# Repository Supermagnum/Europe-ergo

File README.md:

# Europe-ergo
A 94 key ergonomic,split keyboard.
Its powered by 2X Raspberry pico and linked with two 5 pin D sub connectors.
It uses tht components.

The reset switches, 5 pin D sub connectors and raspberry pico's  goes on the reverse side of the Pcb's. 

Picture of Pcb's top side:
https://github.com/Supermagnum/Europe-ergo/blob/main/Europe-ergo-PCB/Europe-ergo-frontside.jpg

Backside:
https://github.com/Supermagnum/Europe-ergo/blob/main/Europe-ergo-PCB/Europe-ergo-backside.jpg

Layout:
https://github.com/Supermagnum/Europe-ergo/blob/main/layout.png

or:

http://www.keyboard-layout-editor.com/#/gists/50db7ea7b0832342d4c734eb985ec16b

The L1/L2 button is to change from  Norwegian QWERTY to Norwegian Dvorak.
There are relevant LEDs that lights up depending on what layer is active.

The NUM key can be used to turn the  num layer on or off.

Keycaps:
https://github.com/Supermagnum/Europe-ergo/blob/main/keycaps.jpg

prototype/"proof of concept" build pictures:
https://github.com/Supermagnum/Europe-ergo/tree/main/prototype-build

Electronic diagram:
https://github.com/Supermagnum/Europe-ergo/blob/main/Europe-ergo-PCB/schema/Europe-ergo.pdf

All mechanical blueprints as pdf files can be exported from the Freecad file.
Freecad can be found for free here:
https://www.freecadweb.org/

PWM1 to PWM 5 controls LED's ( ON/OFF) based by the active layer, and also caps lock and scroll lock active.

Those and the electrical diagram can be found here:
https://github.com/Supermagnum/Europe-ergo/blob/main/Europe-ergo-PCB/schema/Europe-ergo.pdf
The right side has identical outputs for PWM.

Cherry MX switches fit the PCB'S.

Missing from the BOM:
Keyswitch Hotswap sockets: 0305-2-15-80-47-80-10-0 or Digikey: ED90584-ND

STL files for 3D printing or milling of the boxes:
https://github.com/Supermagnum/Europe-ergo/tree/main/mechanical

Tool for aligning the switches under soldering, slips on to the PCB edge an over the switch:
https://github.com/Supermagnum/Europe-ergo/blob/main/mechanical/STL/switch-tool.stl

Panelized version:
https://github.com/Supermagnum/erope-ergo-ex

License:
https://github.com/Supermagnum/Europe-ergo/blob/main/LICENSE

 "

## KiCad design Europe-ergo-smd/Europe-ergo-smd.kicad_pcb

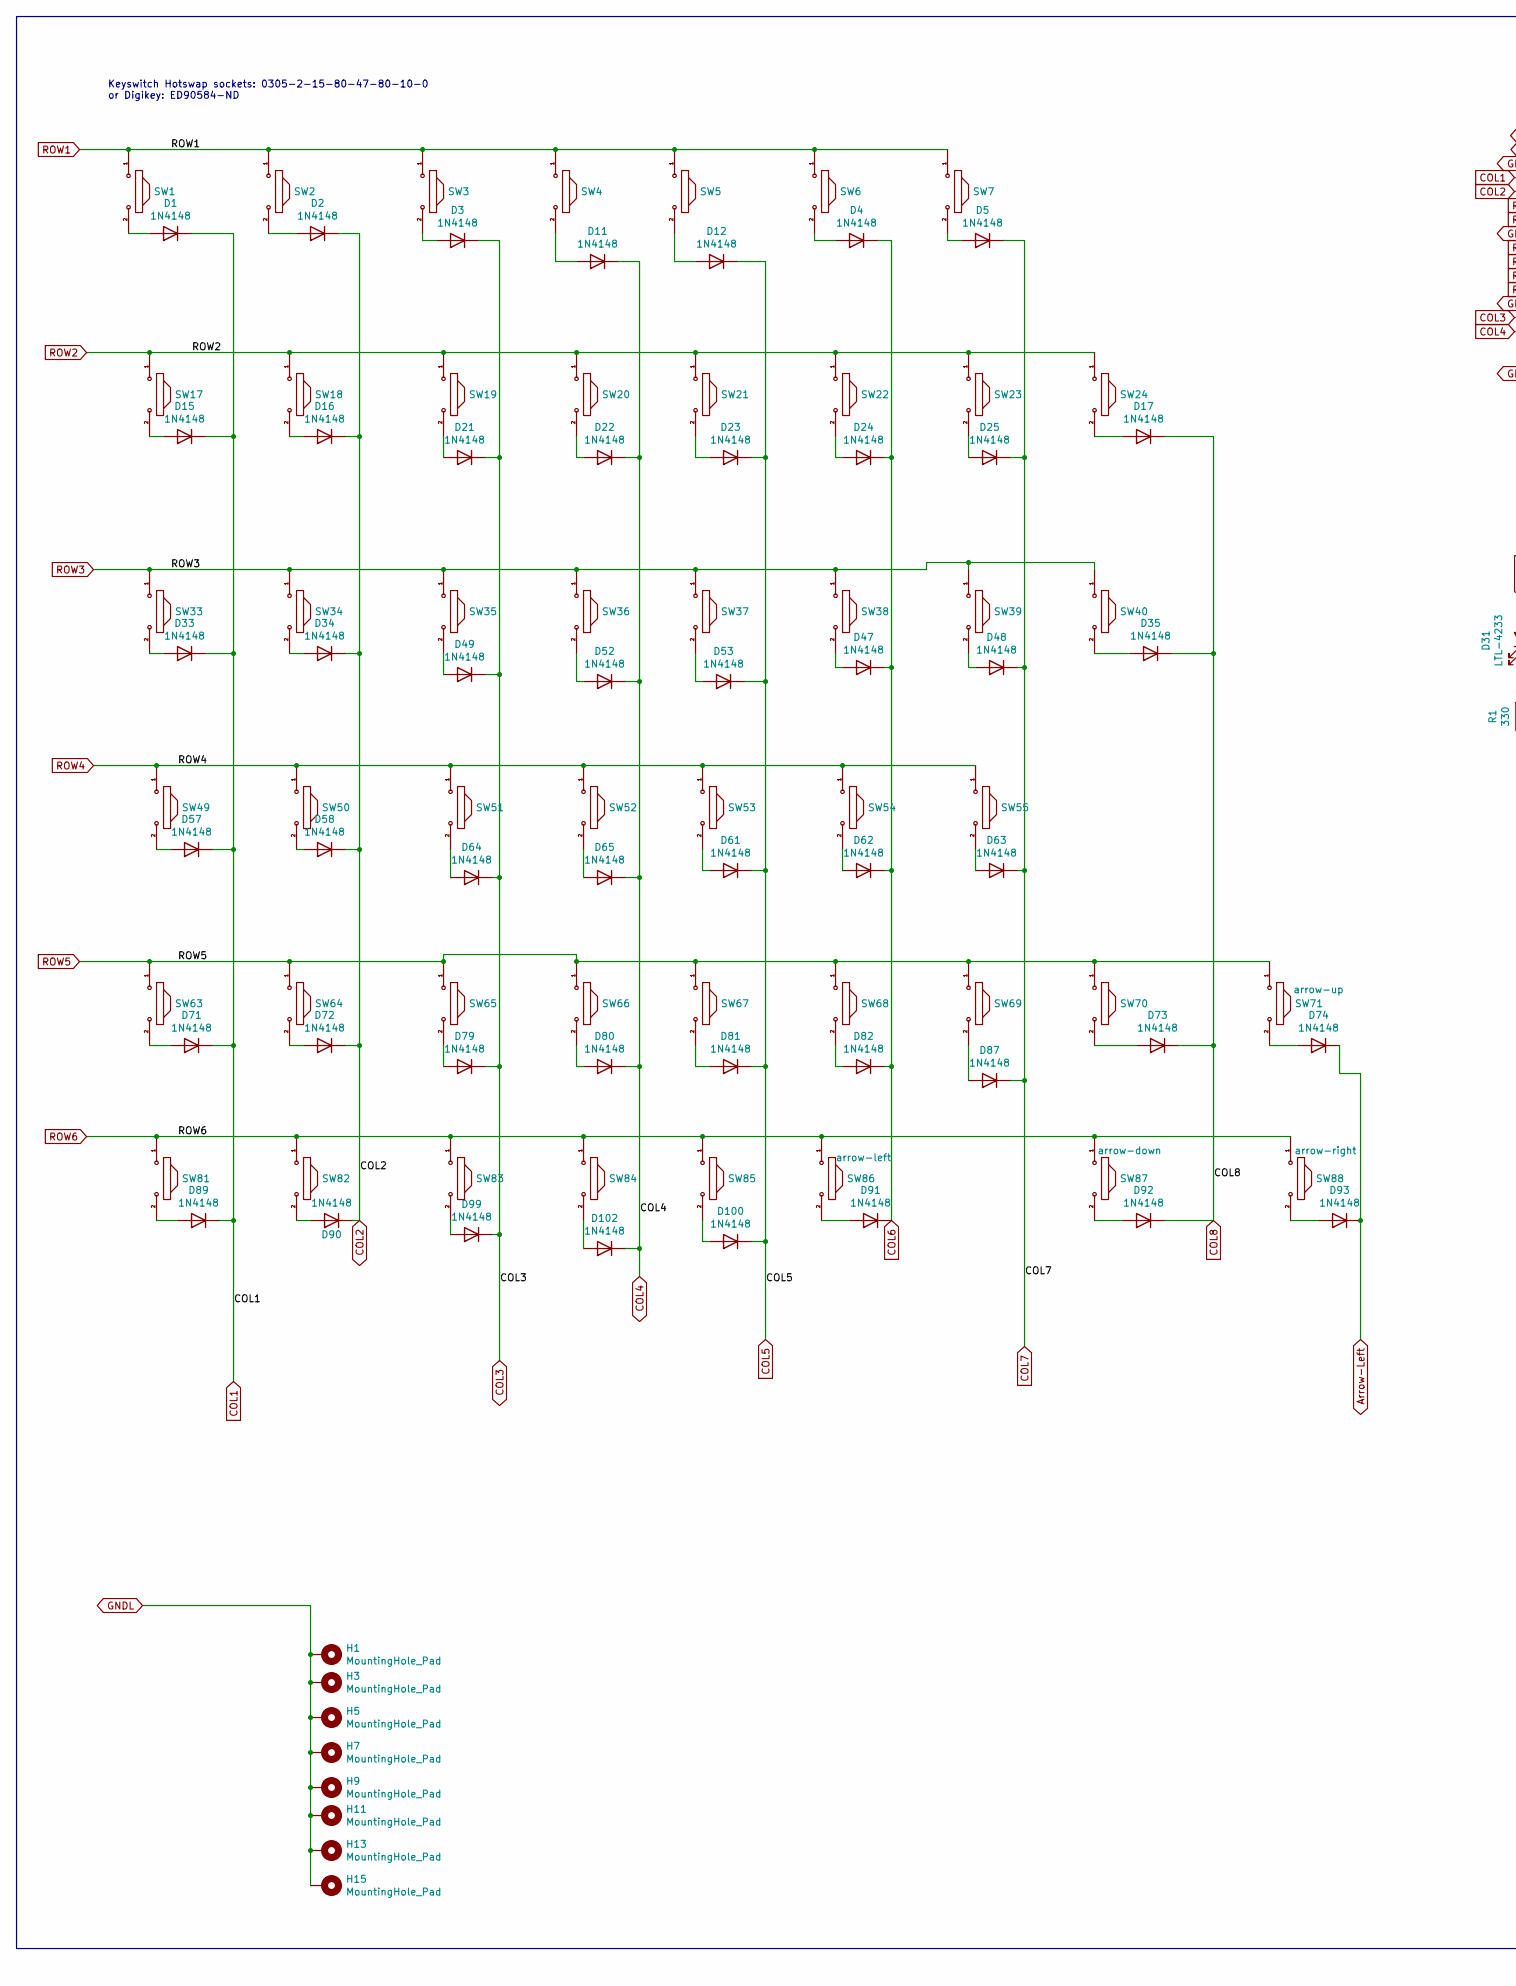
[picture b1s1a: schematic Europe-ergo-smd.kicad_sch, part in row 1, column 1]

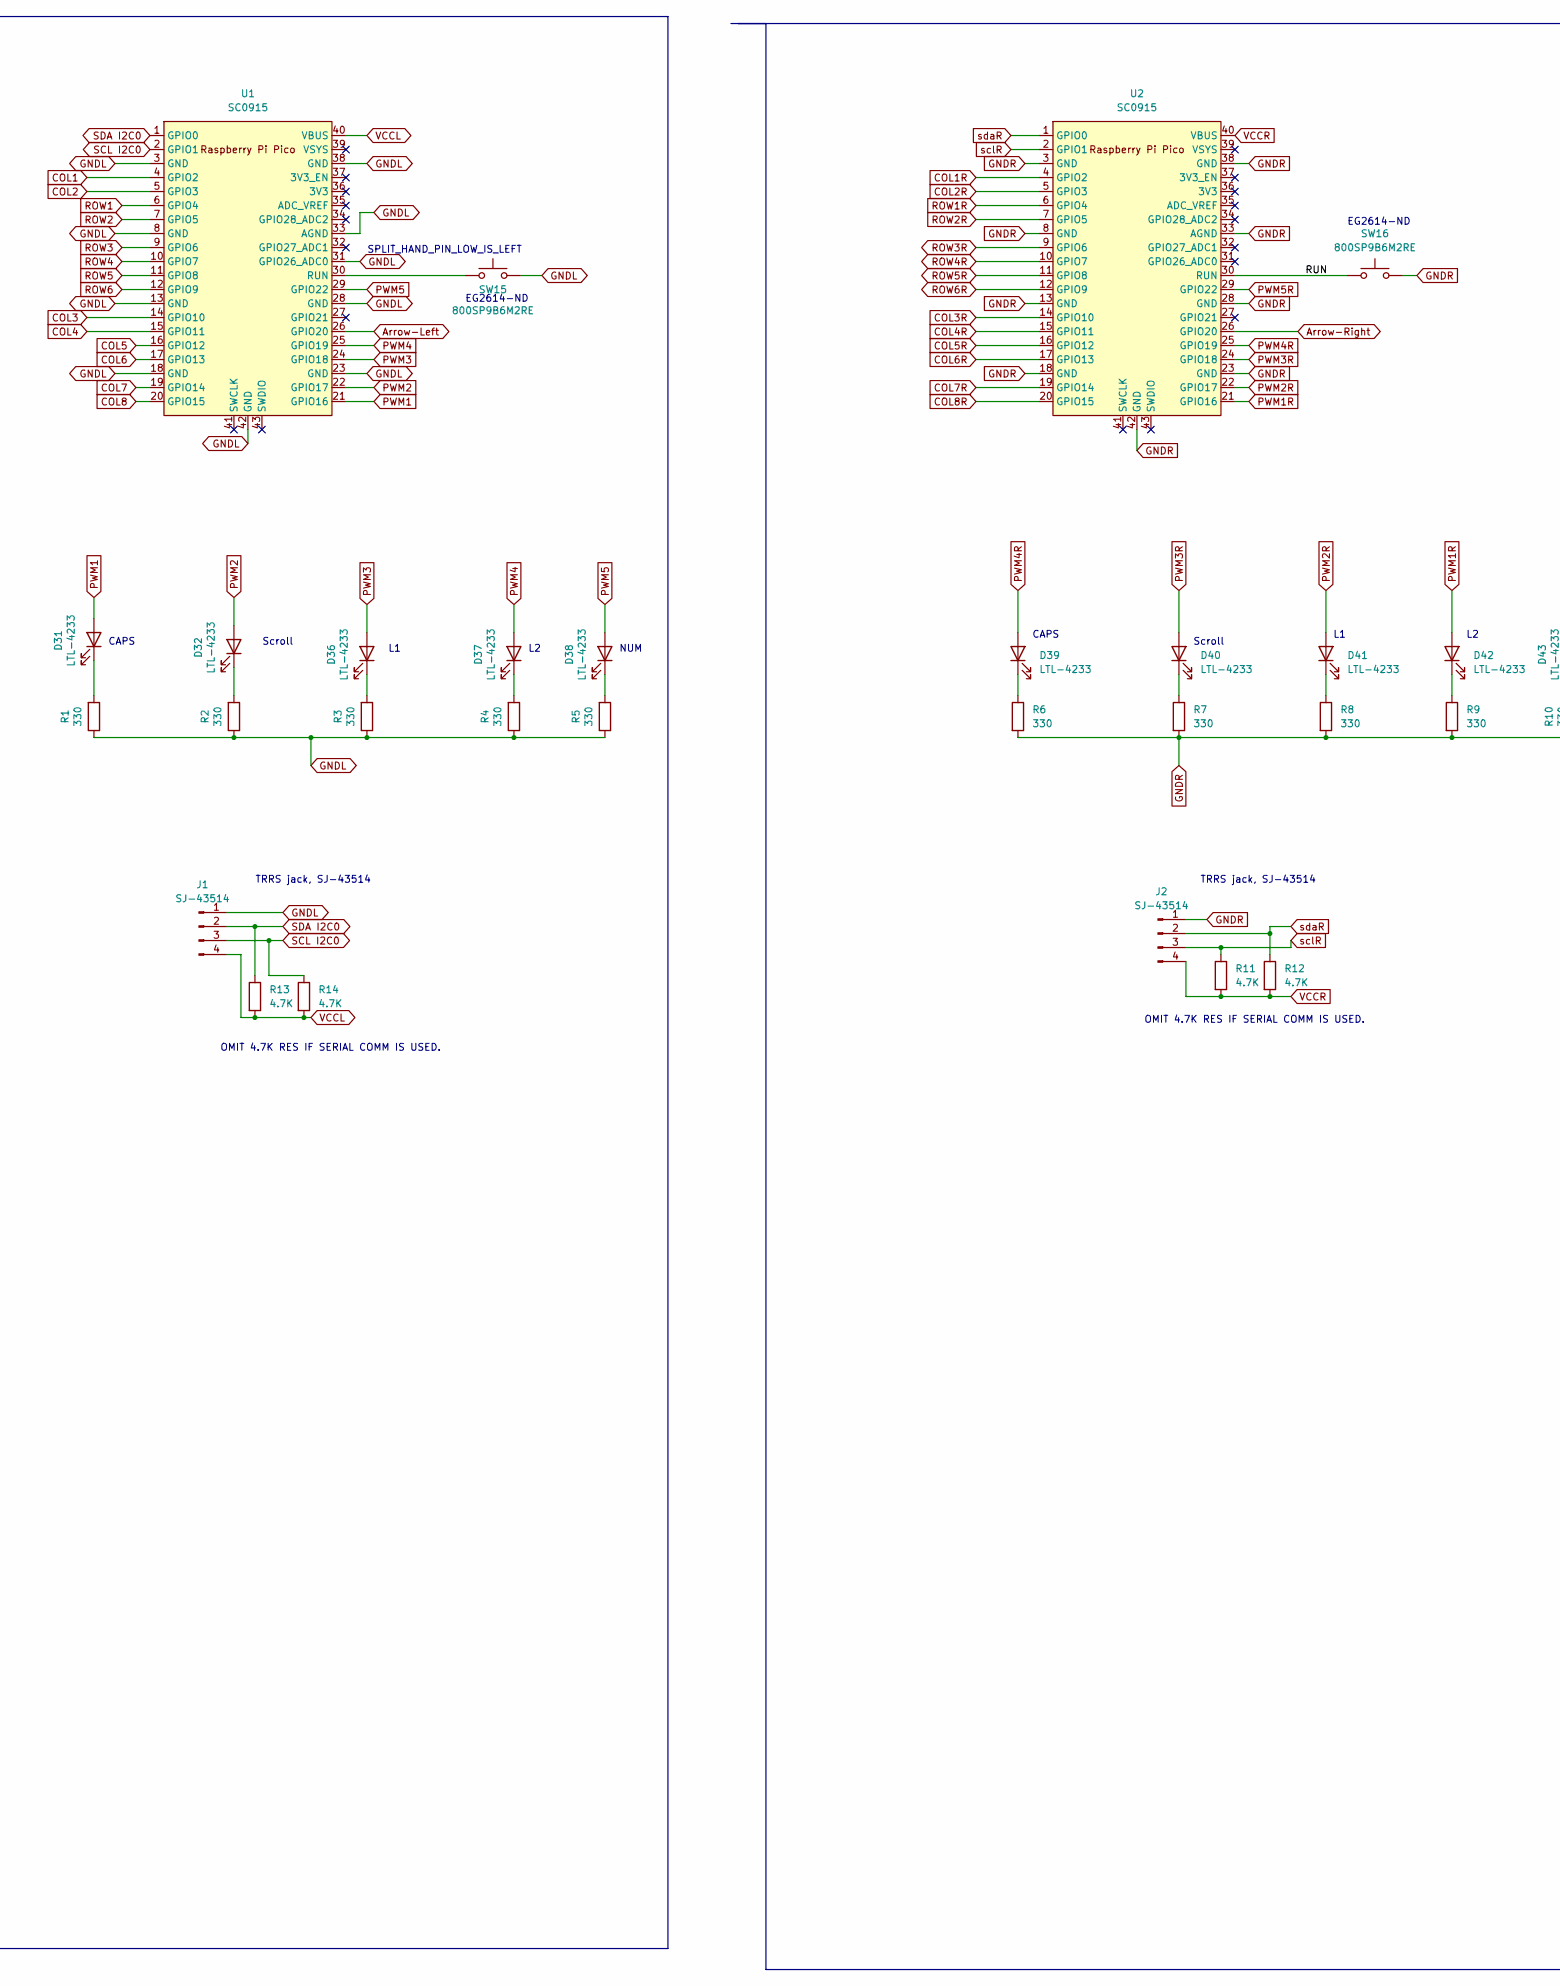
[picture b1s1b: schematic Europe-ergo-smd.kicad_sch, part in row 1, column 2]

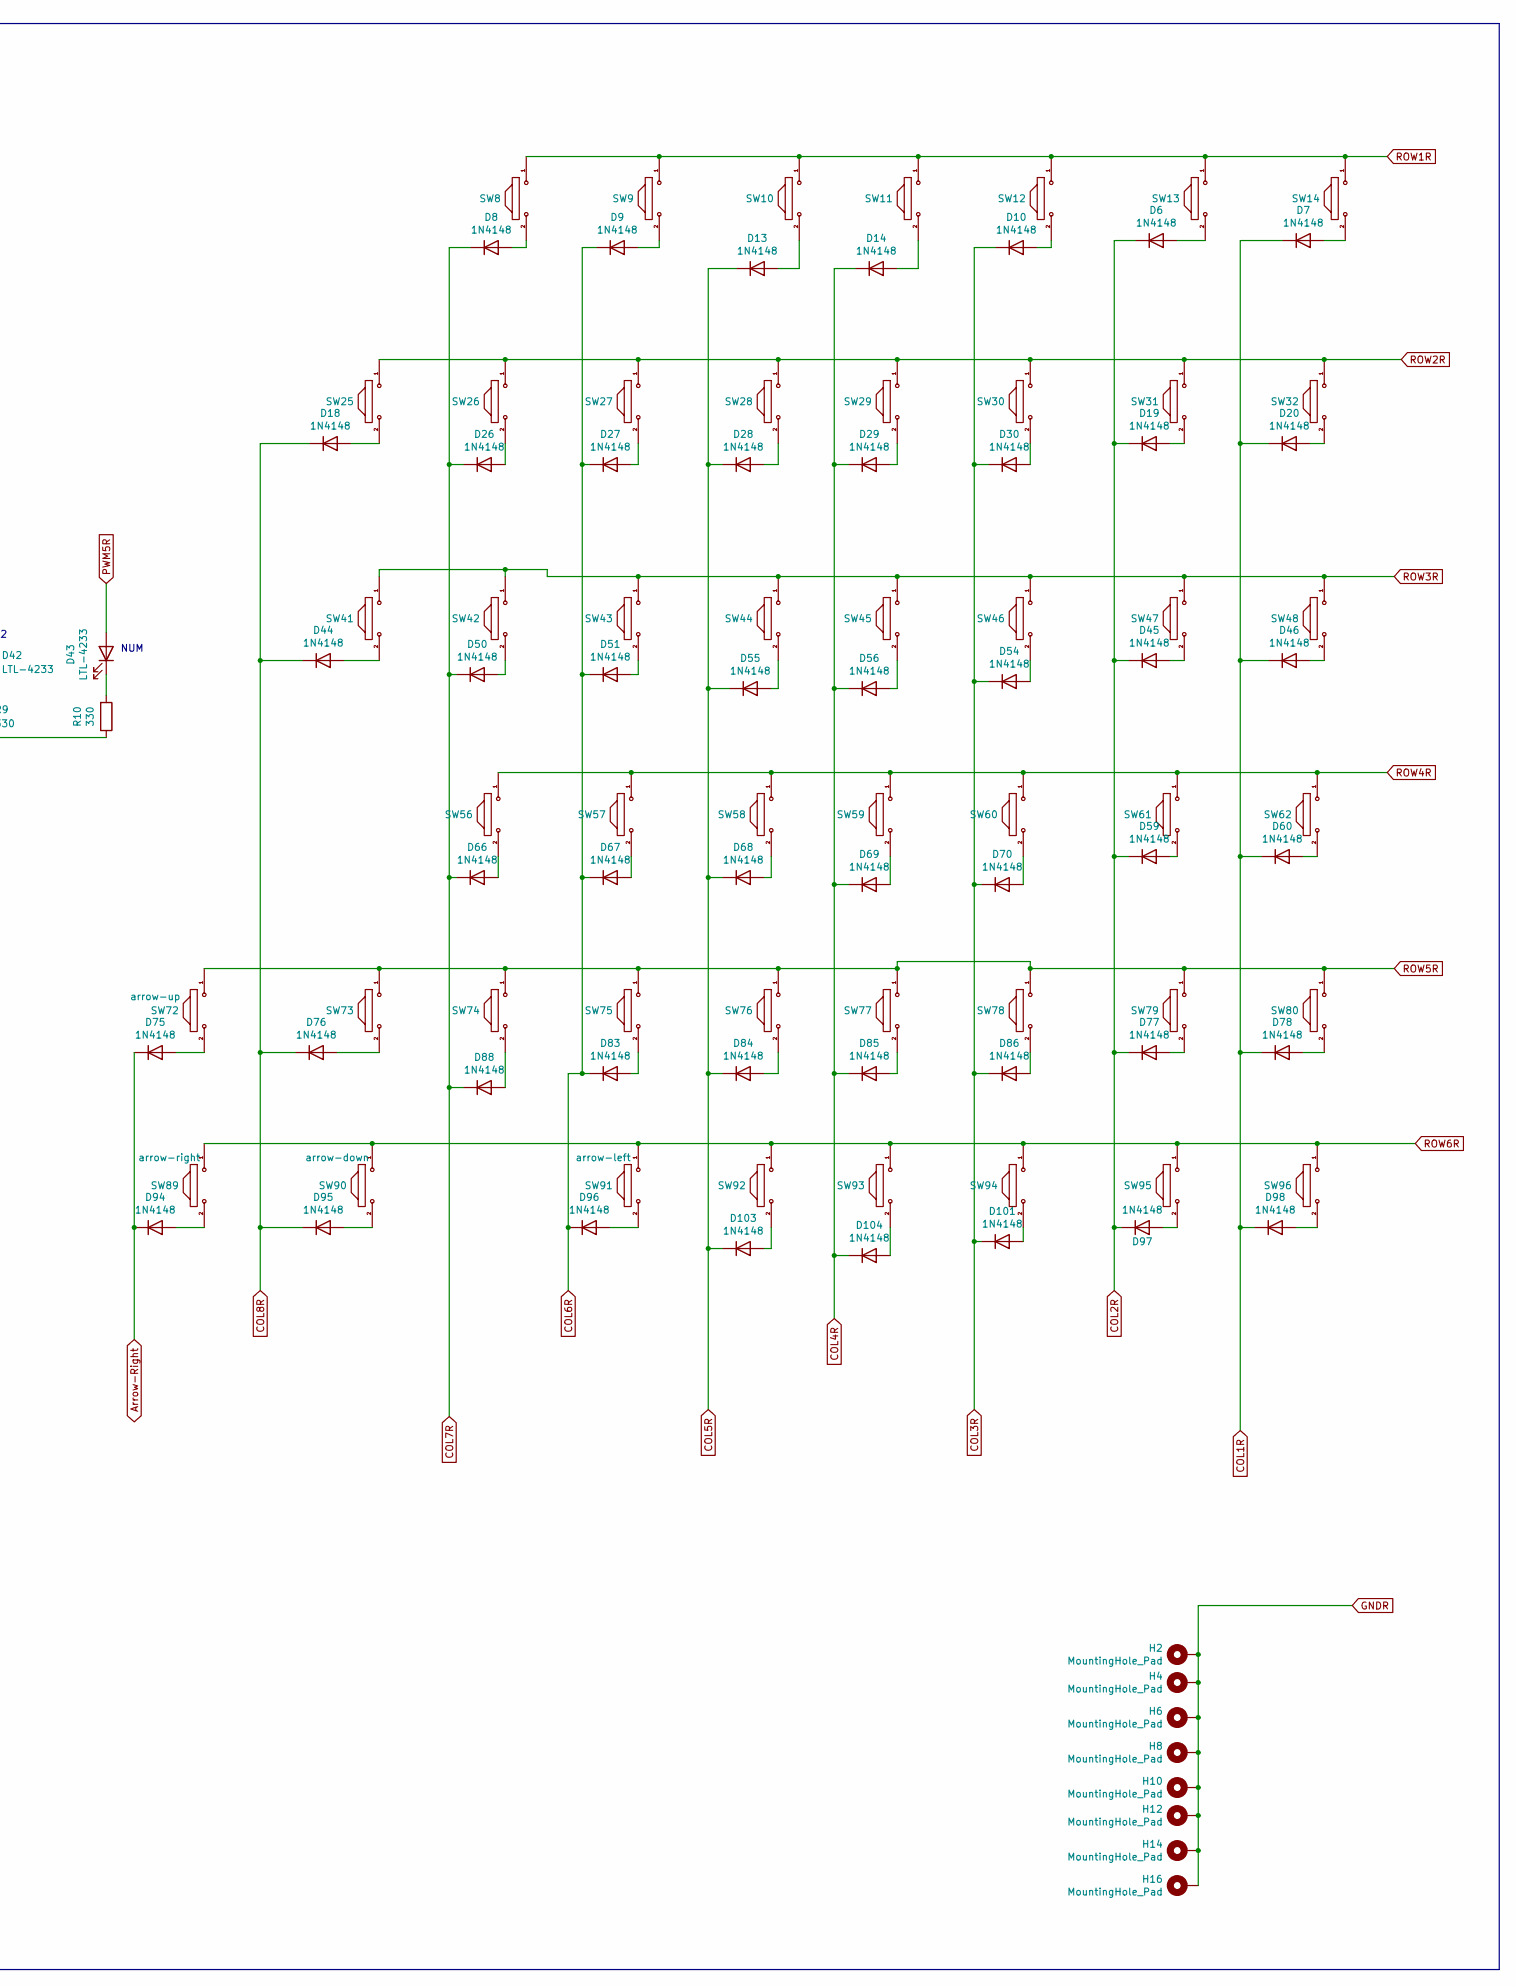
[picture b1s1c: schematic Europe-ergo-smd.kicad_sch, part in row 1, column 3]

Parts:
D1, D2, D3, D4, D5, D6, D7, D8, D9, D10, D11, D12, D13, D14, D15, D16, D17, D18, D19, D20, D21, D22, D23, D24, D25, D26, D27, D28, D29, D30, D33, D34, D35, D44, D45, D46, D47, D48, D49, D50, D51, D52, D53, D54, D55, D56, D57, D58, D59, D60, D61, D62, D63, D64, D65, D66, D67, D68, D69, D70, D71, D72, D73, D74, D75, D76, D77, D78, D79, D80, D81, D82, D83, D84, D85, D86, D87, D88, D89, D90, D91, D92, D93, D94, D95, D96, D97, D98, D99, D100, D101, D102, D103, D104: 1N4148; D_1812_4532Metric
D31, D32, D36, D37, D38, D43: LTL-4233; D_A-405_P2.54mm_Vertical_AnodeUp
D39, D40, D41, D42: LTL-4233; D_DO-34_SOD68_P2.54mm_Vertical_KathodeUp
H1, H2, H3, H4, H5, H6, H7, H8, H9, H10, H11, H12, H13, H14, H15, H16: MountingHole_Pad; MountingHole_4.3mm_M4_DIN965_Pad
J1, J2: SJ-43514; CUI_SJ-43514
R1, R2, R3, R4, R5, R6, R7, R8, R9, R10: 330; R_1812_4532Metric
R11, R12, R13, R14: 4.7K; R_1812_4532Metric
SW1, SW2, SW3, SW4, SW5, SW6, SW7, SW8, SW9, SW10, SW11, SW12, SW13, SW14, SW18, SW19, SW20, SW21, SW22, SW23, SW24, SW25, SW26, SW27, SW28, SW29, SW30, SW31, SW34, SW35, SW36, SW37, SW38, SW39, SW42, SW43, SW44, SW45, SW46, SW47, SW50, SW51, SW52, SW53, SW54, SW55, SW56, SW57, SW58, SW59, SW60, SW61, SW64, SW65, SW66, SW67, SW68, SW69, SW71, SW72, SW74, SW75, SW76, SW77, SW78, SW79, SW81, SW82, SW83, SW84, SW85, SW86, SW87, SW88, SW89, SW90, SW91, SW92, SW93, SW94, SW95, SW96: MX1A-G1NN; SW_Cherry_MX_1.00u_PCB
SW15, SW16: 800SP9B6M2RE; switch_P5.08mm
SW17, SW32, SW33, SW40, SW41, SW48, SW49, SW62, SW63, SW70, SW73, SW80: MX1A-G1NN; SW_Cherry_MX_1.50u_PCB
U1, U2: SC0915; RPi_Pico_SMD_TH

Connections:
/RUN: SW16.1, U2.30 (RUN)
Arrow-Left: D74.1 (K), D93.1 (K), U1.26 (GPIO20)
Arrow-Right: D75.1 (K), D94.1 (K), U2.26 (GPIO20)
COL1: D1.1 (K), D15.1 (K), D33.1 (K), D57.1 (K), D71.1 (K), D89.1 (K), U1.4 (GPIO2)
COL1R: D7.1 (K), D20.1 (K), D46.1 (K), D60.1 (K), D78.1 (K), D98.1 (K), U2.4 (GPIO2)
COL2: D2.1 (K), D16.1 (K), D34.1 (K), D58.1 (K), D72.1 (K), D90.1 (K), U1.5 (GPIO3)
COL2R: D6.1 (K), D19.1 (K), D45.1 (K), D59.1 (K), D77.1 (K), D97.1 (K), U2.5 (GPIO3)
COL3: D3.1 (K), D21.1 (K), D49.1 (K), D64.1 (K), D79.1 (K), D99.1 (K), U1.14 (GPIO10)
COL3R: D10.1 (K), D30.1 (K), D54.1 (K), D70.1 (K), D86.1 (K), D101.1 (K), U2.14 (GPIO10)
COL4: D11.1 (K), D22.1 (K), D52.1 (K), D65.1 (K), D80.1 (K), D102.1 (K), U1.15 (GPIO11)
COL4R: D14.1 (K), D29.1 (K), D56.1 (K), D69.1 (K), D85.1 (K), D104.1 (K), U2.15 (GPIO11)
COL5: D12.1 (K), D23.1 (K), D53.1 (K), D61.1 (K), D81.1 (K), D100.1 (K), U1.16 (GPIO12)
COL5R: D13.1 (K), D28.1 (K), D55.1 (K), D68.1 (K), D84.1 (K), D103.1 (K), U2.16 (GPIO12)
COL6: D4.1 (K), D24.1 (K), D47.1 (K), D62.1 (K), D82.1 (K), D91.1 (K), U1.17 (GPIO13)
COL6R: D9.1 (K), D27.1 (K), D51.1 (K), D67.1 (K), D83.1 (K), D96.1 (K), U2.17 (GPIO13)
COL7: D5.1 (K), D25.1 (K), D48.1 (K), D63.1 (K), D87.1 (K), U1.19 (GPIO14)
COL7R: D8.1 (K), D26.1 (K), D50.1 (K), D66.1 (K), D88.1 (K), U2.19 (GPIO14)
COL8: D17.1 (K), D35.1 (K), D73.1 (K), D92.1 (K), U1.20 (GPIO15)
COL8R: D18.1 (K), D44.1 (K), D76.1 (K), D95.1 (K), U2.20 (GPIO15)
GNDL: H1.1, H3.1, H5.1, H7.1, H9.1, H11.1, H13.1, H15.1, J1.1, R1.1, R2.1, R3.1, R4.1, R5.1, SW15.2, U1.3 (GND), U1.8 (GND), U1.13 (GND), U1.18 (GND), U1.23 (GND), U1.28 (GND), U1.31 (GPIO26_ADC0), U1.33 (AGND), U1.38 (GND), U1.42 (GND)
GNDR: H2.1, H4.1, H6.1, H8.1, H10.1, H12.1, H14.1, H16.1, J2.1, R6.2, R7.2, R8.2, R9.2, R10.1, SW16.2, U2.3 (GND), U2.8 (GND), U2.13 (GND), U2.18 (GND), U2.23 (GND), U2.28 (GND), U2.33 (AGND), U2.38 (GND), U2.42 (GND)
unnamed: D1.2 (A), SW1.2
unnamed: D2.2 (A), SW2.2
unnamed: D3.2 (A), SW3.2
unnamed: D4.2 (A), SW6.2
unnamed: D5.2 (A), SW7.2
unnamed: D6.2 (A), SW13.2
unnamed: D7.2 (A), SW14.2
unnamed: D8.2 (A), SW8.2
unnamed: D9.2 (A), SW9.2
unnamed: D10.2 (A), SW12.2
unnamed: D11.2 (A), SW4.2
unnamed: D12.2 (A), SW5.2
unnamed: D13.2 (A), SW10.2
unnamed: D14.2 (A), SW11.2
unnamed: D15.2 (A), SW17.2
unnamed: D16.2 (A), SW18.2
unnamed: D17.2 (A), SW24.2
unnamed: D18.2 (A), SW25.2
unnamed: D19.2 (A), SW31.2
unnamed: D20.2 (A), SW32.2
unnamed: D21.2 (A), SW19.2
unnamed: D22.2 (A), SW20.2
unnamed: D23.2 (A), SW21.2
unnamed: D24.2 (A), SW22.2
unnamed: D25.2 (A), SW23.2
unnamed: D26.2 (A), SW26.2
unnamed: D27.2 (A), SW27.2
unnamed: D28.2 (A), SW28.2
unnamed: D29.2 (A), SW29.2
unnamed: D30.2 (A), SW30.2
unnamed: D31.1 (K), R1.2
unnamed: D32.1 (K), R2.2
unnamed: D33.2 (A), SW33.2
unnamed: D34.2 (A), SW34.2
unnamed: D35.2 (A), SW40.2
unnamed: D36.1 (K), R3.2
unnamed: D37.1 (K), R4.2
unnamed: D38.1 (K), R5.2
unnamed: D39.1 (K), R6.1
unnamed: D40.1 (K), R7.1
unnamed: D41.1 (K), R8.1
unnamed: D42.1 (K), R9.1
unnamed: D43.1 (K), R10.2
unnamed: D44.2 (A), SW41.2
unnamed: D45.2 (A), SW47.2
unnamed: D46.2 (A), SW48.2
unnamed: D47.2 (A), SW38.2
unnamed: D48.2 (A), SW39.2
unnamed: D49.2 (A), SW35.2
unnamed: D50.2 (A), SW42.2
unnamed: D51.2 (A), SW43.2
unnamed: D52.2 (A), SW36.2
unnamed: D53.2 (A), SW37.2
unnamed: D54.2 (A), SW46.2
unnamed: D55.2 (A), SW44.2
unnamed: D56.2 (A), SW45.2
unnamed: D57.2 (A), SW49.2
unnamed: D58.2 (A), SW50.2
unnamed: D59.2 (A), SW61.2
unnamed: D60.2 (A), SW62.2
unnamed: D61.2 (A), SW53.2
unnamed: D62.2 (A), SW54.2
unnamed: D63.2 (A), SW55.2
unnamed: D64.2 (A), SW51.2
unnamed: D65.2 (A), SW52.2
unnamed: D66.2 (A), SW56.2
unnamed: D67.2 (A), SW57.2
unnamed: D68.2 (A), SW58.2
unnamed: D69.2 (A), SW59.2
unnamed: D70.2 (A), SW60.2
unnamed: D71.2 (A), SW63.2
unnamed: D72.2 (A), SW64.2
unnamed: D73.2 (A), SW70.2
unnamed: D74.2 (A), SW71.2
unnamed: D75.2 (A), SW72.2
unnamed: D76.2 (A), SW73.2
unnamed: D77.2 (A), SW79.2
unnamed: D78.2 (A), SW80.2
unnamed: D79.2 (A), SW65.2
unnamed: D80.2 (A), SW66.2
unnamed: D81.2 (A), SW67.2
unnamed: D82.2 (A), SW68.2
unnamed: D83.2 (A), SW75.2
unnamed: D84.2 (A), SW76.2
unnamed: D85.2 (A), SW77.2
unnamed: D86.2 (A), SW78.2
unnamed: D87.2 (A), SW69.2
unnamed: D88.2 (A), SW74.2
unnamed: D89.2 (A), SW81.2
unnamed: D90.2 (A), SW82.2
unnamed: D91.2 (A), SW86.2
unnamed: D92.2 (A), SW87.2
unnamed: D93.2 (A), SW88.2
unnamed: D94.2 (A), SW89.2
unnamed: D95.2 (A), SW90.2
unnamed: D96.2 (A), SW91.2
unnamed: D97.2 (A), SW95.2
unnamed: D98.2 (A), SW96.2
unnamed: D99.2 (A), SW83.2
unnamed: D100.2 (A), SW85.2
unnamed: D101.2 (A), SW94.2
unnamed: D102.2 (A), SW84.2
unnamed: D103.2 (A), SW92.2
unnamed: D104.2 (A), SW93.2
unnamed: SW15.1, U1.30 (RUN)
PWM1: D31.2 (A), U1.21 (GPIO16)
PWM1R: D42.2 (A), U2.21 (GPIO16)
PWM2: D32.2 (A), U1.22 (GPIO17)
PWM2R: D41.2 (A), U2.22 (GPIO17)
PWM3: D36.2 (A), U1.24 (GPIO18)
PWM3R: D40.2 (A), U2.24 (GPIO18)
PWM4: D37.2 (A), U1.25 (GPIO19)
PWM4R: D39.2 (A), U2.25 (GPIO19)
PWM5: D38.2 (A), U1.29 (GPIO22)
PWM5R: D43.2 (A), U2.29 (GPIO22)
ROW1: SW1.1, SW2.1, SW3.1, SW4.1, SW5.1, SW6.1, SW7.1, U1.6 (GPIO4)
ROW1R: SW8.1, SW9.1, SW10.1, SW11.1, SW12.1, SW13.1, SW14.1, U2.6 (GPIO4)
ROW2: SW17.1, SW18.1, SW19.1, SW20.1, SW21.1, SW22.1, SW23.1, SW24.1, U1.7 (GPIO5)
ROW2R: SW25.1, SW26.1, SW27.1, SW28.1, SW29.1, SW30.1, SW31.1, SW32.1, U2.7 (GPIO5)
ROW3: SW33.1, SW34.1, SW35.1, SW36.1, SW37.1, SW38.1, SW39.1, SW40.1, U1.9 (GPIO6)
ROW3R: SW41.1, SW42.1, SW43.1, SW44.1, SW45.1, SW46.1, SW47.1, SW48.1, U2.9 (GPIO6)
ROW4: SW49.1, SW50.1, SW51.1, SW52.1, SW53.1, SW54.1, SW55.1, U1.10 (GPIO7)
ROW4R: SW56.1, SW57.1, SW58.1, SW59.1, SW60.1, SW61.1, SW62.1, U2.10 (GPIO7)
ROW5: SW63.1, SW64.1, SW65.1, SW66.1, SW67.1, SW68.1, SW69.1, SW70.1, SW71.1, U1.11 (GPIO8)
ROW5R: SW72.1, SW73.1, SW74.1, SW75.1, SW76.1, SW77.1, SW78.1, SW79.1, SW80.1, U2.11 (GPIO8)
ROW6: SW81.1, SW82.1, SW83.1, SW84.1, SW85.1, SW86.1, SW87.1, SW88.1, U1.12 (GPIO9)
ROW6R: SW89.1, SW90.1, SW91.1, SW92.1, SW93.1, SW94.1, SW95.1, SW96.1, U2.12 (GPIO9)
SCL I2C0: J1.3, R14.1, U1.2 (GPIO1)
SDA I2C0: J1.2, R13.1, U1.1 (GPIO0)
VCCL: J1.4, R13.2, R14.2, U1.40 (VBUS)
VCCR: J2.4, R11.2, R12.2, U2.40 (VBUS)
sclR: J2.3, R11.1, U2.2 (GPIO1)
sdaR: J2.2, R12.1, U2.1 (GPIO0)

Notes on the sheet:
EG2614-ND
Keyswitch Hotswap sockets: 0305-2-15-80-47-80-10-0 or Digikey: ED90584-ND
CAPS
Scroll
OMIT 4.7K RES IF SERIAL COMM IS USED.
SPLIT_HAND_PIN_LOW_IS_LEFT
NUM
TRRS jack, SJ-43514

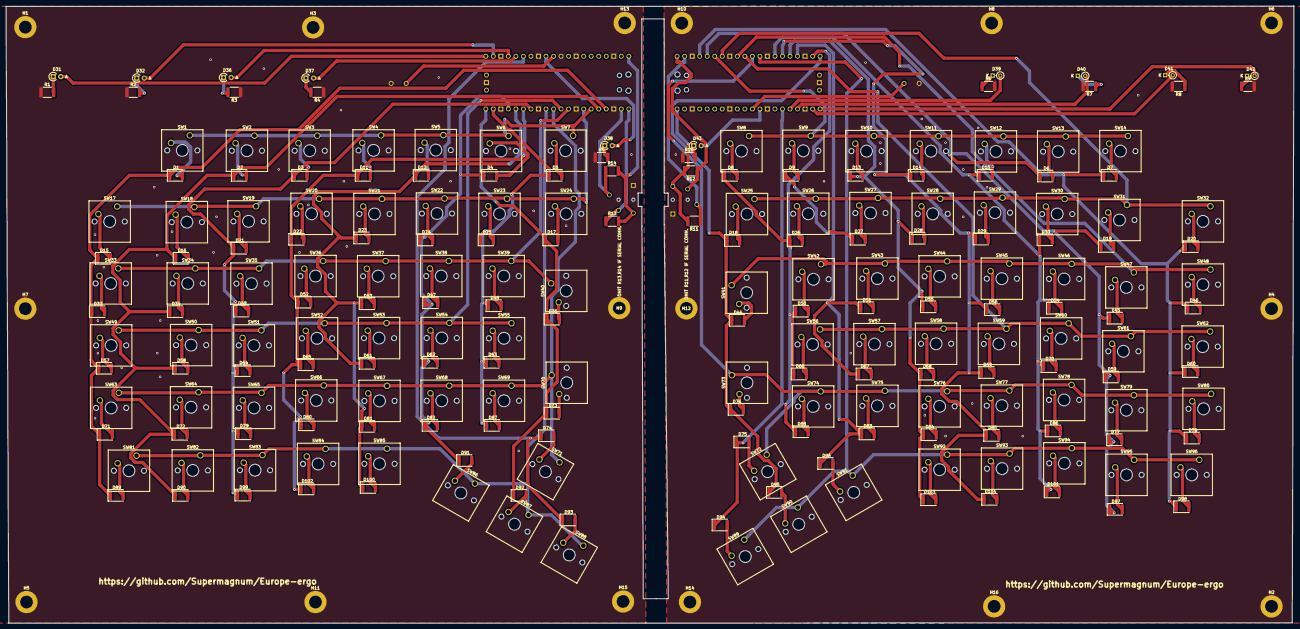
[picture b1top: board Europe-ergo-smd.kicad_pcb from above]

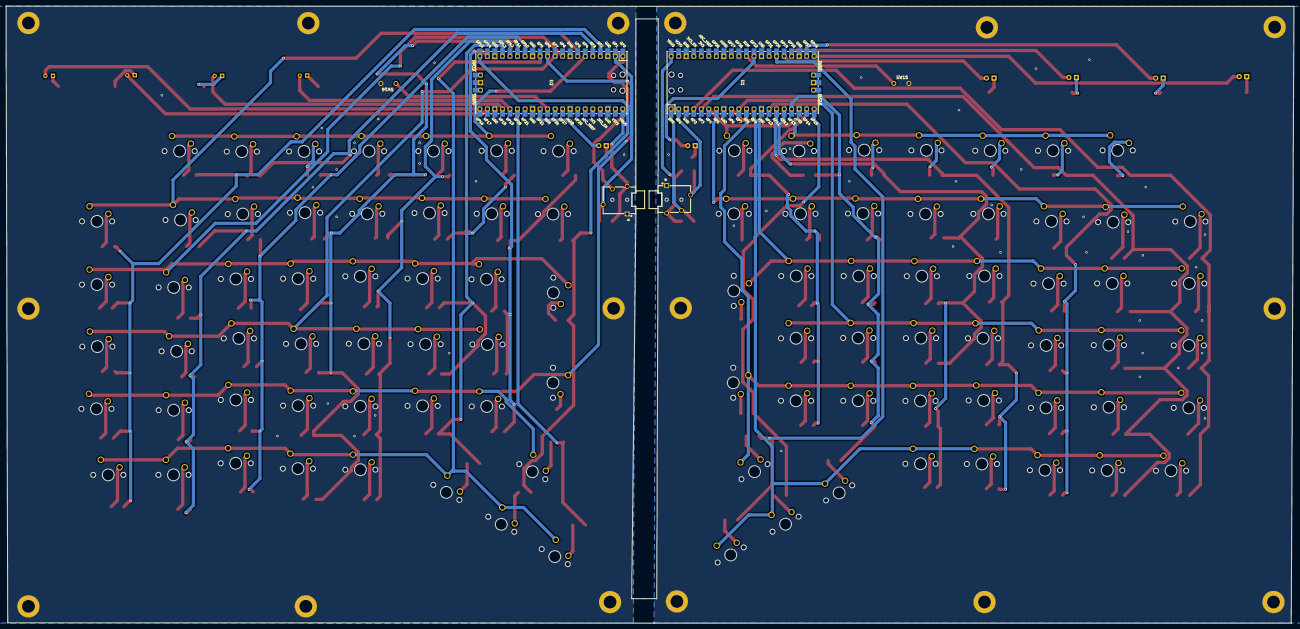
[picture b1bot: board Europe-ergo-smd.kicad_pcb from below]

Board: 2 copper layers, 434.5 x 208.2 mm, 234 parts (6 on the bottom side), 154 nets.

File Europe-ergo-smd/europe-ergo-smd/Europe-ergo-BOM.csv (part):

Source:,/mnt/b955457f-512b-4f44-a0f7-8e5f2b78aba2/Europe-ergo/Europe-ergo-PCB/Europe-ergo.kicad_sch,,,,,,
Date:,fr. 20. jan. 2023 kl. 16.28 +0100,,,,,,
Tool:,Eeschema 6.0.10-86aedd382b~118~ubuntu22.04.1,,,,,,
Generator:,/usr/share/kicad/plugins/bom_csv_grouped_by_value.py,,,,,,
Component Count:,230,,,,,,
,,,,,,,
Individual Components:,,,,,,,
,,,,,,,
Item,Qty,Reference(s),Value,LibPart,Footprint,Datasheet,Field4
,,D1,1N4148,Diode:1N4148,Diode_THT:D_DO-35_SOD27_P7.62mm_Horizontal,https://assets.nexperia.com/documents/data-sheet/1N4148_1N4448.pdf,
,,D2,1N4148,Diode:1N4148,Diode_THT:D_DO-35_SOD27_P7.62mm_Horizontal,https://assets.nexperia.com/documents/data-sheet/1N4148_1N4448.pdf,
,,D3,1N4148,Diode:1N4148,Diode_THT:D_DO-35_SOD27_P7.62mm_Horizontal,https://assets.nexperia.com/documents/data-sheet/1N4148_1N4448.pdf,
,,D4,1N4148,Diode:1N4148,Diode_THT:D_DO-35_SOD27_P7.62mm_Horizontal,https://assets.nexperia.com/documents/data-sheet/1N4148_1N4448.pdf,
,,D5,1N4148,Diode:1N4148,Diode_THT:D_DO-35_SOD27_P7.62mm_Horizontal,https://assets.nexperia.com/documents/data-sheet/1N4148_1N4448.pdf,
,,D6,1N4148,Diode:1N4148,Diode_THT:D_DO-35_SOD27_P7.62mm_Horizontal,https://assets.nexperia.com/documents/data-sheet/1N4148_1N4448.pdf,
,,D7,1N4148,Diode:1N4148,Diode_THT:D_DO-35_SOD27_P7.62mm_Horizontal,https://assets.nexperia.com/documents/data-sheet/1N4148_1N4448.pdf,
,,D8,1N4148,Diode:1N4148,Diode_THT:D_DO-35_SOD27_P7.62mm_Horizontal,https://assets.nexperia.com/documents/data-sheet/1N4148_1N4448.pdf,
,,D9,1N4148,Diode:1N4148,Diode_THT:D_DO-35_SOD27_P7.62mm_Horizontal,https://assets.nexperia.com/documents/data-sheet/1N4148_1N4448.pdf,
,,D10,1N4148,Diode:1N4148,Diode_THT:D_DO-35_SOD27_P7.62mm_Horizontal,https://assets.nexperia.com/documents/data-sheet/1N4148_1N4448.pdf,
,,D11,1N4148,Diode:1N4148,Diode_THT:D_DO-35_SOD27_P7.62mm_Horizontal,https://assets.nexperia.com/documents/data-sheet/1N4148_1N4448.pdf,
,,D12,1N4148,Diode:1N4148,Diode_THT:D_DO-35_SOD27_P7.62mm_Horizontal,https://assets.nexperia.com/documents/data-sheet/1N4148_1N4448.pdf,
,,D13,1N4148,Diode:1N4148,Diode_THT:D_DO-35_SOD27_P7.62mm_Horizontal,https://assets.nexperia.com/documents/data-sheet/1N4148_1N4448.pdf,
,,D14,1N4148,Diode:1N4148,Diode_THT:D_DO-35_SOD27_P7.62mm_Horizontal,https://assets.nexperia.com/documents/data-sheet/1N4148_1N4448.pdf,
,,D15,1N4148,Diode:1N4148,Diode_THT:D_DO-35_SOD27_P7.62mm_Horizontal,https://assets.nexperia.com/documents/data-sheet/1N4148_1N4448.pdf,
,,D16,1N4148,Diode:1N4148,Diode_THT:D_DO-35_SOD27_P7.62mm_Horizontal,https://assets.nexperia.com/documents/data-sheet/1N4148_1N4448.pdf,
,,D17,1N4148,Diode:1N4148,Diode_THT:D_DO-35_SOD27_P7.62mm_Horizontal,https://assets.nexperia.com/documents/data-sheet/1N4148_1N4448.pdf,
,,D18,1N4148,Diode:1N4148,Diode_THT:D_DO-35_SOD27_P7.62mm_Horizontal,https://assets.nexperia.com/documents/data-sheet/1N4148_1N4448.pdf,
,,D19,1N4148,Diode:1N4148,Diode_THT:D_DO-35_SOD27_P7.62mm_Horizontal,https://assets.nexperia.com/documents/data-sheet/1N4148_1N4448.pdf,
,,D20,1N4148,Diode:1N4148,Diode_THT:D_DO-35_SOD27_P7.62mm_Horizontal,https://assets.nexperia.com/documents/data-sheet/1N4148_1N4448.pdf,
,,D21,1N4148,Diode:1N4148,Diode_THT:D_DO-35_SOD27_P7.62mm_Horizontal,https://assets.nexperia.com/documents/data-sheet/1N4148_1N4448.pdf,
,,D22,1N4148,Diode:1N4148,Diode_THT:D_DO-35_SOD27_P7.62mm_Horizontal,https://assets.nexperia.com/documents/data-sheet/1N4148_1N4448.pdf,
,,D23,1N4148,Diode:1N4148,Diode_THT:D_DO-35_SOD27_P7.62mm_Horizontal,https://assets.nexperia.com/documents/data-sheet/1N4148_1N4448.pdf,
,,D24,1N4148,Diode:1N4148,Diode_THT:D_DO-35_SOD27_P7.62mm_Horizontal,https://assets.nexperia.com/documents/data-sheet/1N4148_1N4448.pdf,
,,D25,1N4148,Diode:1N4148,Diode_THT:D_DO-35_SOD27_P7.62mm_Horizontal,https://assets.nexperia.com/documents/data-sheet/1N4148_1N4448.pdf,
,,D26,1N4148,Diode:1N4148,Diode_THT:D_DO-35_SOD27_P7.62mm_Horizontal,https://assets.nexperia.com/documents/data-sheet/1N4148_1N4448.pdf,
,,D27,1N4148,Diode:1N4148,Diode_THT:D_DO-35_SOD27_P7.62mm_Horizontal,https://assets.nexperia.com/documents/data-sheet/1N4148_1N4448.pdf,
,,D28,1N4148,Diode:1N4148,Diode_THT:D_DO-35_SOD27_P7.62mm_Horizontal,https://assets.nexperia.com/documents/data-sheet/1N4148_1N4448.pdf,
,,D29,1N4148,Diode:1N4148,Diode_THT:D_DO-35_SOD27_P7.62mm_Horizontal,https://assets.nexperia.com/documents/data-sheet/1N4148_1N4448.pdf,
,,D30,1N4148,Diode:1N4148,Diode_THT:D_DO-35_SOD27_P7.62mm_Horizontal,https://assets.nexperia.com/documents/data-sheet/1N4148_1N4448.pdf,
,,D31,1N4148,Diode:1N4148,Diode_THT:D_DO-35_SOD27_P7.62mm_Horizontal,https://assets.nexperia.com/documents/data-sheet/1N4148_1N4448.pdf,
,,D32,1N4148,Diode:1N4148,Diode_THT:D_DO-35_SOD27_P7.62mm_Horizontal,https://assets.nexperia.com/documents/data-sheet/1N4148_1N4448.pdf,
,,D33,1N4148,Diode:1N4148,Diode_THT:D_DO-35_SOD27_P7.62mm_Horizontal,https://assets.nexperia.com/documents/data-sheet/1N4148_1N4448.pdf,
,,D34,1N4148,Diode:1N4148,Diode_THT:D_DO-35_SOD27_P7.62mm_Horizontal,https://assets.nexperia.com/documents/data-sheet/1N4148_1N4448.pdf,
,,D35,1N4148,Diode:1N4148,Diode_THT:D_DO-35_SOD27_P7.62mm_Horizontal,https://assets.nexperia.com/documents/data-sheet/1N4148_1N4448.pdf,
,,D36,1N4148,Diode:1N4148,Diode_THT:D_DO-35_SOD27_P7.62mm_Horizontal,https://assets.nexperia.com/documents/data-sheet/1N4148_1N4448.pdf,
,,D37,1N4148,Diode:1N4148,Diode_THT:D_DO-35_SOD27_P7.62mm_Horizontal,https://assets.nexperia.com/documents/data-sheet/1N4148_1N4448.pdf,
,,D38,1N4148,Diode:1N4148,Diode_THT:D_DO-35_SOD27_P7.62mm_Horizontal,https://assets.nexperia.com/documents/data-sheet/1N4148_1N4448.pdf,
,,D39,1N4148,Diode:1N4148,Diode_THT:D_DO-35_SOD27_P7.62mm_Horizontal,https://assets.nexperia.com/documents/data-sheet/1N4148_1N4448.pdf,
,,D40,1N4148,Diode:1N4148,Diode_THT:D_DO-35_SOD27_P7.62mm_Horizontal,https://assets.nexperia.com/documents/data-sheet/1N4148_1N4448.pdf,
,,D41,1N4148,Diode:1N4148,Diode_THT:D_DO-35_SOD27_P7.62mm_Horizontal,https://assets.nexperia.com/documents/data-sheet/1N4148_1N4448.pdf,
,,D42,1N4148,Diode:1N4148,Diode_THT:D_DO-35_SOD27_P7.62mm_Horizontal,https://assets.nexperia.com/documents/data-sheet/1N4148_1N4448.pdf,
,,D43,1N4148,Diode:1N4148,Diode_THT:D_DO-35_SOD27_P7.62mm_Horizontal,https://assets.nexperia.com/documents/data-sheet/1N4148_1N4448.pdf,
,,D44,1N4148,Diode:1N4148,Diode_THT:D_DO-35_SOD27_P7.62mm_Horizontal,https://assets.nexperia.com/documents/data-sheet/1N4148_1N4448.pdf,
,,D45,1N4148,Diode:1N4148,Diode_THT:D_DO-35_SOD27_P7.62mm_Horizontal,https://assets.nexperia.com/documents/data-sheet/1N4148_1N4448.pdf,
,,D46,1N4148,Diode:1N4148,Diode_THT:D_DO-35_SOD27_P7.62mm_Horizontal,https://assets.nexperia.com/documents/data-sheet/1N4148_1N4448.pdf,
,,D47,1N4148,Diode:1N4148,Diode_THT:D_DO-35_SOD27_P7.62mm_Horizontal,https://assets.nexperia.com/documents/data-sheet/1N4148_1N4448.pdf,
,,D48,LTL-4233 ,Device:LED,Diode_THT:D_DO-34_SOD68_P2.54mm_Vertical_KathodeUp,~,
,,D49,LTL-4233 ,Device:LED,Diode_THT:D_DO-34_SOD68_P2.54mm_Vertical_KathodeUp,~,
,,D50,LTL-4233 ,Device:LED,Diode_THT:D_DO-34_SOD68_P2.54mm_Vertical_KathodeUp,~,
,,D51,LTL-4233 ,Device:LED,Diode_THT:D_DO-34_SOD68_P2.54mm_Vertical_KathodeUp,~,
,,D52,LTL-4233 ,Device:LED,Diode_THT:D_A-405_P2.54mm_Vertical_AnodeUp,~,
,,D53,LTL-4233 ,Device:LED,Diode_THT:D_A-405_P2.54mm_Vertical_AnodeUp,~,
,,D54,LTL-4233 ,Device:LED,Diode_THT:D_A-405_P2.54mm_Vertical_AnodeUp,~,
,,D55,LTL-4233 ,Device:LED,Diode_THT:D_A-405_P2.54mm_Vertical_AnodeUp,~,
,,D56,1N4148,Diode:1N4148,Diode_THT:D_DO-35_SOD27_P7.62mm_Horizontal,https://assets.nexperia.com/documents/data-sheet/1N4148_1N4448.pdf,
,,D57,1N4148,Diode:1N4148,Diode_THT:D_DO-35_SOD27_P7.62mm_Horizontal,https://assets.nexperia.com/documents/data-sheet/1N4148_1N4448.pdf,
,,D58,1N4148,Diode:1N4148,Diode_THT:D_DO-35_SOD27_P7.62mm_Horizontal,https://assets.nexperia.com/documents/data-sheet/1N4148_1N4448.pdf,
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
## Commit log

2022-12-05 Add files via upload
    upload because of name change.
2022-12-05 Add files via upload
    Upload firmware.
2022-12-05 Add files via upload
    fixed some naming errors.
2022-12-05 Add files via upload
    Moved the MCU and reset switch to the reverse side of the pcb.
2022-12-05 Add files via upload
    updated stl files.
2022-12-08 Update README.md
    Update
2022-12-09 Update europe_ergo.h
    Add license header
2022-12-09 Update keymap.c
    Added license header.
2022-12-09 Update config.h
    Added license header
2022-12-09 Update readme.md
    Correction
2022-12-09 Update LICENSE
    License change to match License Headers.
2022-12-09 Add files via upload
    updated files
2022-12-09 Add files via upload
    Fixed some small issues
2022-12-09 Update BOM.txt
    updated parts list.
2023-01-15 Add files via upload
    small fix
2023-02-16 Add files via upload
    Moved switches footprints closer.
2023-03-02 Add files via upload
    added freecad file and stl files.
2023-03-23 Add files via upload
    Added a default keymap file that implements the NUM layer, and controls the relevant LED.
2023-04-27 Update keymap.c
    Fixed deprecated values.
2023-05-24 Add files via upload
    update
2023-06-08 Update keymap.c
    Enabled debug, and changed to KC_TRANSPARENT .
2023-06-17 Update README.md
    update and clean up of old files.
2023-06-21 Update keymap.c
    Added debugging to check if all keys register correctly when pressed.
2023-06-21 Update keymap.c
    changed values to match keymap values from here:
    https://github.com/qmk/qmk_firmware/blob/master/quantum/keymap_extras/keymap_norwegian.h
2023-06-22 Create layout.json
    converted from KLE
2023-06-26 Update keymap.c
    appended a new layer
2023-06-26 wrote a short test file, to check
2023-06-28 added prototype picture
2023-06-29 Update info.json
    removed comments
2023-07-01 Update info.json
    Added right side reversal
2023-07-01 Update keymap.c
    Added debug.
2023-07-03 Add files via upload
    upload of old firmware.
2023-07-07 Update config.h
    Added options for proper PCB.
2023-07-07 Add files via upload
    Changed the column information to be correct.
2023-07-07 Update info.json
    fixed colum error
2023-07-07 Update info.json
    Removed typo.
2023-07-07 Add files via upload
    Added row information.
2023-07-11 Add files via upload
    Made a test keymap
2023-07-12 Added debug information
    Issues are at row 5, 10 and 11. These prints wrong characters.
2023-07-12 Update info.json
    Tab needs to be cleaned up.
2023-07-20 Update info.json
    fixed tab spaces
2023-07-20 Update keymap.c
    fixed right menu key issue
2023-07-25 Update keymap.c
    added LED initialization
2023-07-25 Update keymap.c
    added housekeeping_task_user()
2023-07-28 Update keymap.c
    Changed _NORWEGIAN To Norwegian Dvorak.
    Deactivated letters on the NUM layer.
    changed some keys to space.
2023-08-03 Update keymap.c
    fixed wrong arrow keys.
2023-08-03 Update keymap.c
    small fix
2023-08-10 Create test
2023-08-10 Add files via upload
    Pictures from prototype build process.
